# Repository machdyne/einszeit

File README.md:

# Einszeit

Einszeit is an open-source security device intended to provide information-theoretically secure (one-time-pad based) encryption between two or more paired devices over any communications medium.

> **Project status:** V1 hardware is in active development. See [Hardware Status](#hardware-status) and [Software Status](#software-status) below before using this project for anything beyond bench testing.

## Hardware Status

**V1: design complete, hardware tested.** Built around the RP2350 microcontroller. Boards have been fabricated, bench validated and entropy-tested. The design files are in `pcb/einszeit_v1` (schematic: `pcb/einszeit_v1.pdf`).

### Architecture

V1 is built around the **RP2350** microcontroller, chosen primarily for its documented, dedicated TRNG peripheral.

- **Entropy source:** RP2350's built-in TRNG block (Arm IP), which samples an internal free-running ring oscillator and claims compliance with FIPS 140-2, BSI AIS-31, and NIST SP 800-90B. Nominal entropy rate is ~7.5 kb/s at 150 MHz core clock.
- **Key storage:** key material never leaves the device, except on a microSD card, which is also how keys are exchanged.

### Why a raw TRNG

One-time-pad key material needs close to full entropy in every output bit. The random number generator of a typical secure element is not a raw entropy tap: it is the output of an internal DRBG (deterministic random bit generator), seeded periodically from a physical noise source. Its output entropy is bounded by the infrequently refreshed seed, not by the number of bytes read out, so it is architecturally unsuited to one-time-pad keys. Einszeit therefore uses the RP2350's TRNG, whose raw output can be tested directly.

One limitation remains: the TRNG is closed Arm IP, so its internal construction cannot be independently validated.

A secondary, physically independent entropy source (e.g. a discrete noise circuit) is not currently planned, but remains a possible future defense-in-depth addition if the RP2350 TRNG's characteristics warrant it.

Full entropy source documentation, extraction method, and validation results have been published alongside V1 firmware.

## Software Status

V1 software is complete enough for bench use with two devices, and is being tested on V1 hardware. It is not yet audited: do not use it for real secrets.

- **The device's terminal interface.** Connect any terminal program (PuTTY, screen, minicom, Tera Term) to the device's USB serial port:
  - Home shows the device at a glance;
  - Keys is a key manager: new keys, import and export on a transfer card, spare copies, delete;
  - Send and Receive encrypt and decrypt messages of up to 64 KiB, typed or pasted, or transferred as files by ZMODEM or XMODEM (detected automatically).

  See the [user interface document](docs/einszeit-ui.md) (EZ-UI-001).
- **`ez`, the host CLI** (`sw/ez`), over USB HID: scripting, and messages above 64 KiB. Build with `cmake -S sw -B build/sw && cmake --build build/sw`.
- **Firmware images** (`fw/einszeit`):
  - `einszeit_composite`: the terminal interface plus `ez`;
  - `einszeit_cdc`: the terminal interface only;
  - `einszeit_hid`: `ez` only.

  None of them has a software path into the bootloader; this is checked at build time. `einszeit_dev` adds development commands and hardware tests, and must never be used for real secrets.
- **Where keys are kept:**
  - on the **card** (microSD), in two copies, which the device checks and repairs by itself (the card mirror);
  - in the device's **internal storage**, alone or as a **spare copy** of a card key.

  Every 4 KiB of key is checked against its integrity tag before use, so a damaged or wrong card can cost a key but never secrecy. Keys leave the device only on a card.
- **A portable core** (`core/`), shared by the firmware and the host tests: offsets committed to F-RAM before any key byte is used, quarantine, an event log, key generation with online entropy monitoring, and buffered and streaming encryption.
- **Testing:**
  - on the host (`tests/run.sh`) against simulated hardware, with power loss, bit flips and card removal at every step;
  - an SD card emulator running the firmware's own driver;
  - screen tests of the terminal interface;
  - interoperability tests of the file transfers against lrzsz;
  - fuzzing.

  See [tests/README.md](tests/README.md).

Still open: the entropy assessment (OI-04), Windows support (OI-05), and an audit. See the [open items](docs/einszeit-implementation-spec.md#13-open-items).

Specifications and records: [security requirements](docs/einszeit-security-requirements.md) (EZ-SEC-001), [implementation specification](docs/einszeit-implementation-spec.md) (EZ-IMPL-001), [user interface](docs/einszeit-ui.md) (EZ-UI-001), [entropy thresholds](docs/einszeit-entropy-thresholds.md), [deviations](docs/einszeit-deviations.md) (EZ-DEV-001), [traceability](docs/einszeit-traceability.md) (EZ-TRACE-001).

## Security Model

Einszeit's core claim is that, given genuine full-entropy key material and correct one-time use, message confidentiality is information-theoretically secure — i.e., secure regardless of an adversary's computational power. This claim depends entirely on:

1. The entropy source(s) actually delivering full min-entropy per output bit (not merely passing statistical randomness tests, which a well-built DRBG would also pass).
2. Conditioning/extraction functions that don't reintroduce a computational-hardness dependency where an information-theoretic one is claimed (e.g., preferring universal-hash/Leftover-Hash-Lemma-based extraction over hash-based conditioning where the strict claim matters).
3. Correct one-time use of key material and secure erasure after use.

## AI Disclosure

This project makes use of LLMs for documentation, specifications, firmware and software. Once the project is stable, a human audit will be performed resulting in a code freeze that must not be directly modified by any LLM without an additional human audit. See our [GenAI session summaries](docs/genai).

## Funding

This project was partially funded through the NGI0 Commons Fund, a fund established by NLnet with financial support from the European Commission's Next Generation Internet programme.

## License

The contents of this repo are released under the [CERN-OHL-P](LICENSE.txt) license with the following exceptions:

 * The hidapi library (`sw/hidapi.c`, `sw/hidapi.h`) is BSD licensed.
 * The FatFs library (`third_party/fatfs`) is released under the FatFs license by ChaN, a 1-clause BSD-style license; see [third_party/fatfs/LICENSE.txt](third_party/fatfs/LICENSE.txt).
 * The Zetta editor (`third_party/zetta`) is released under the BSD-1-Clause license; see [third_party/zetta/LICENSE.md](third_party/zetta/LICENSE.md).

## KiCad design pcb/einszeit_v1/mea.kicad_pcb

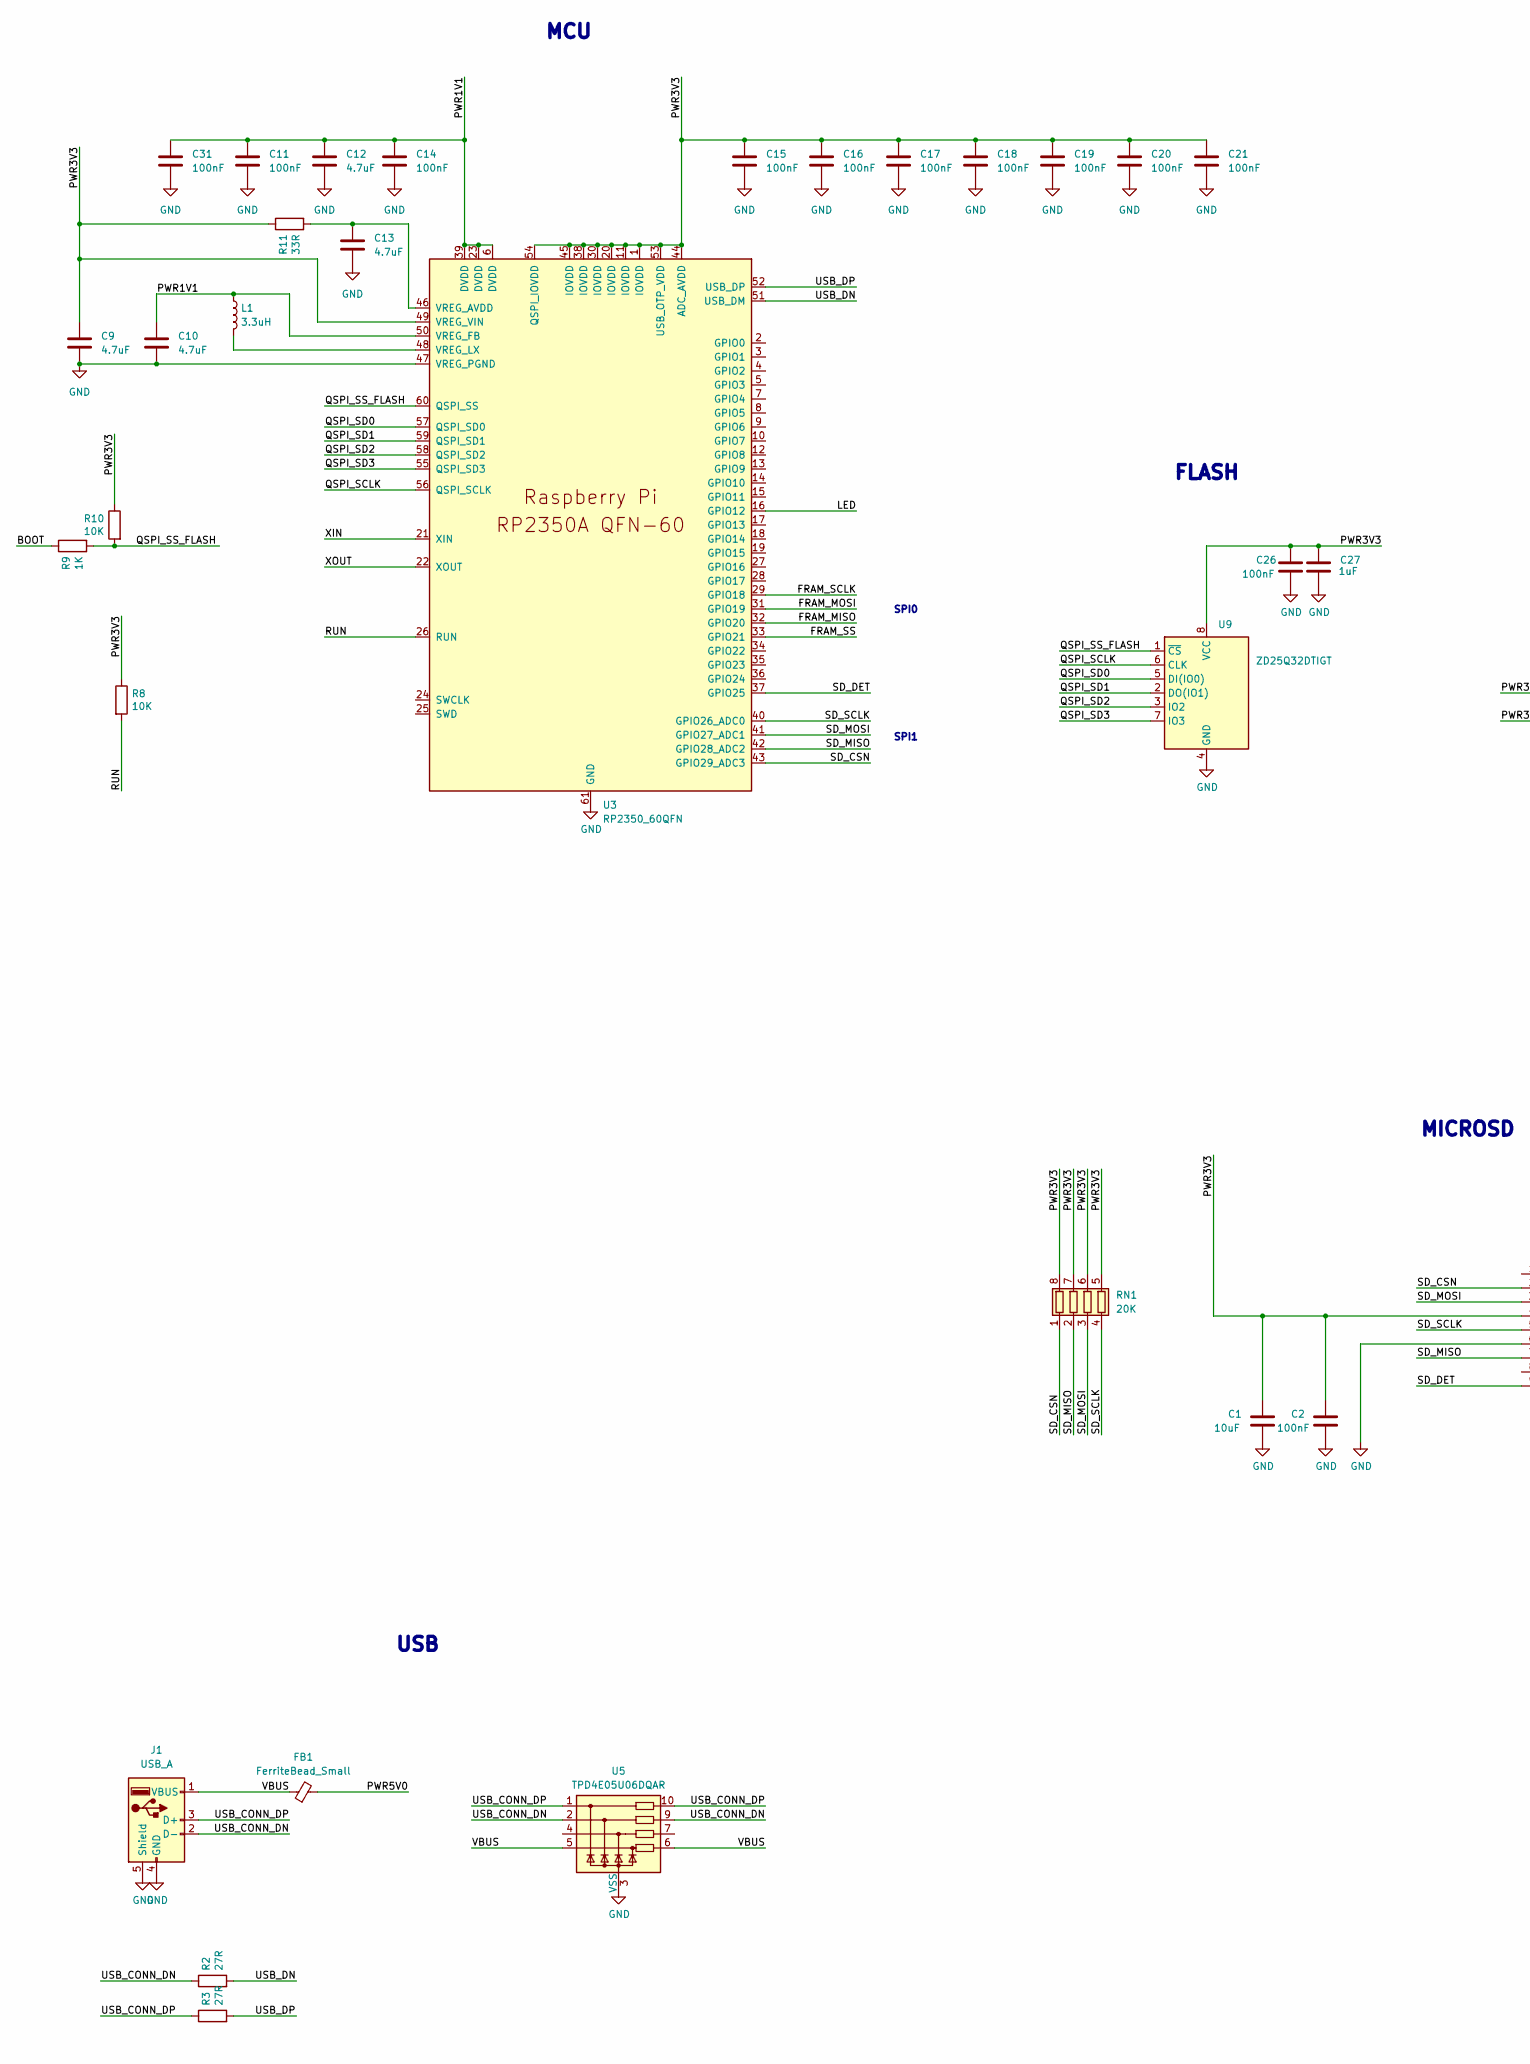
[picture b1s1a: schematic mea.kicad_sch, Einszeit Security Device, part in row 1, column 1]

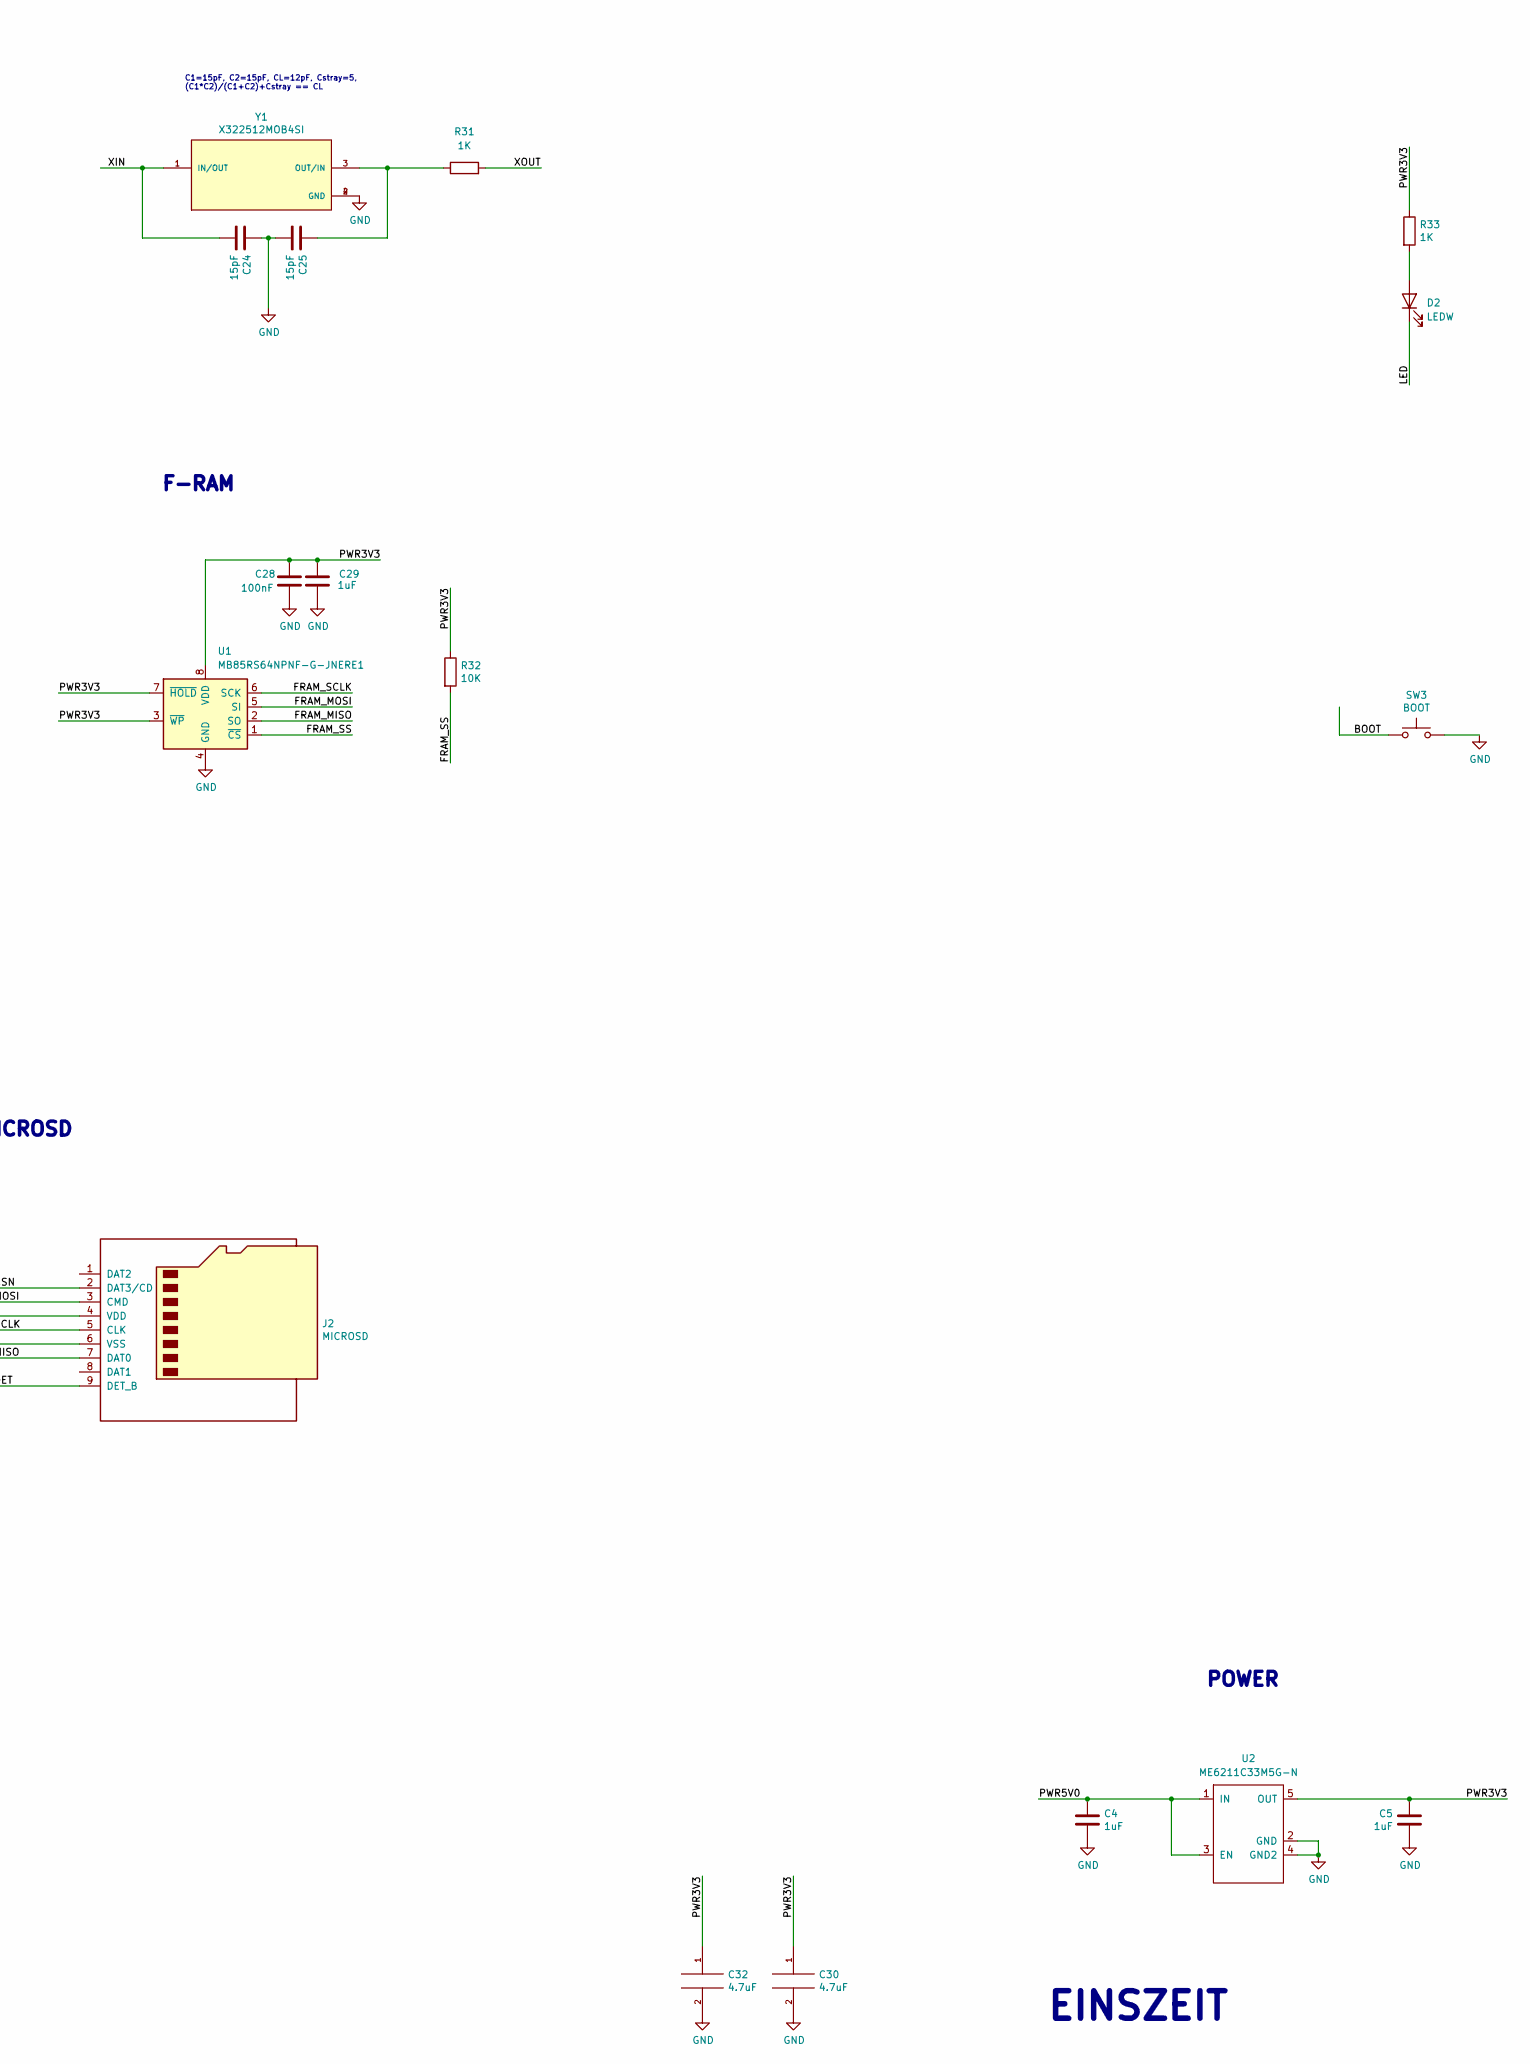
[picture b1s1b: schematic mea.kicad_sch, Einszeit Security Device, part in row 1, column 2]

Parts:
C1: 10uF; C_0402_1005Metric
C2, C11, C14, C15, C16, C17, C18, C19, C20, C21, C26, C28, C31: 100nF; C_0402_1005Metric
C4, C5, C27, C29: 1uF; C_0402_1005Metric
C9, C10, C12, C13, C30, C32: 4.7uF; C_0402_1005Metric
C24, C25: 15pF; C_0402_1005Metric
D2: LEDW; LED_0603_1608Metric
FB1: FerriteBead_Small; R_0402_1005Metric
J1: USB_A; USB_A_CNCTech_1001-011-01101_Horizontal
J2: MICROSD; TF-018B-H15-HAND-SOLDER
L1: 3.3uH; L_Murata_DFE201610P
R2, R3: 27R; R_0402_1005Metric
R8, R10, R32: 10K; R_0402_1005Metric
R9, R31, R33: 1K; R_0402_1005Metric
R11: 33R; R_0402_1005Metric
RN1: 20K; R_Array_Convex_4x0402
SW3: BOOT; Button_2P_3x4mm
U1: MB85RS64NPNF-G-JNERE1; SOIC-8_3.9x4.9mm_P1.27mm
U2: ME6211C33M5G-N; TSOP-5_1.65x3.05mm_P0.95mm
U3: RP2350_60QFN; RP2350-QFN-60-1EP_7x7_P0.4mm_EP3.4x3.4mm_ThermalVias
U5: TPD4E05U06DQAR; Diodes_UDFN-10_1.0x2.5mm_P0.5mm
U9: ZD25Q32DTIGT; SOIC-8_3.9x4.9mm_P1.27mm
Y1: X322512MOB4SI; XTAL_ECS-240-8-33-AGN-TR

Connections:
/BOOT: R9.1, SW3.1
/FRAM_MISO: U1.2 (SO), U3.32 (GPIO20)
/FRAM_MOSI: U1.5 (SI), U3.31 (GPIO19)
/FRAM_SCLK: U1.6 (SCK), U3.29 (GPIO18)
/FRAM_SS: R32.2, U1.1 (~CS), U3.33 (GPIO21)
/LED: D2.1 (K), U3.16 (GPIO12)
/PWR1V1: C10.1, C11.1, C12.1, C14.1, C31.1, L1.1, U3.6 (DVDD), U3.23 (DVDD), U3.39 (DVDD), U3.50 (VREG_FB)
/PWR3V3: C1.1, C2.1, C5.1, C9.1, C15.1, C16.1, C17.1, C18.1, C19.1, C20.1, C21.1, C26.1, C27.1, C28.1, C29.1, C30.1, C32.1, J2.4 (VDD), R8.1, R10.1, R11.1, R32.1, R33.1, RN1.5 (R4.2), RN1.6 (R3.2), RN1.7 (R2.2), RN1.8 (R1.2), U1.3 (~WP), U1.7 (~HOLD), U1.8 (VDD), U2.5 (OUT), U3.1 (IOVDD), U3.11 (IOVDD), U3.20 (IOVDD), U3.30 (IOVDD), U3.38 (IOVDD), U3.44 (ADC_AVDD), U3.45 (IOVDD), U3.49 (VREG_VIN), U3.53 (USB_OTP_VDD), U3.54 (QSPI_IOVDD), U9.8 (VCC)
/PWR5V0: C4.1, FB1.2, U2.1 (IN), U2.3 (EN)
/QSPI_SCLK: U3.56 (QSPI_SCLK), U9.6 (CLK)
/QSPI_SD0: U3.57 (QSPI_SD0), U9.5 (DI(IO0))
/QSPI_SD1: U3.59 (QSPI_SD1), U9.2 (DO(IO1))
/QSPI_SD2: U3.58 (QSPI_SD2), U9.3 (IO2)
/QSPI_SD3: U3.55 (QSPI_SD3), U9.7 (IO3)
/QSPI_SS_FLASH: R9.2, R10.2, U3.60 (QSPI_SS), U9.1 (~CS)
/RUN: R8.2, U3.26 (RUN)
/SD_CSN: J2.2 (DAT3/CD), RN1.1 (R1.1), U3.43 (GPIO29_ADC3)
/SD_DET: J2.9 (DET_B), U3.37 (GPIO25)
/SD_MISO: J2.7 (DAT0), RN1.2 (R2.1), U3.42 (GPIO28_ADC2)
/SD_MOSI: J2.3 (CMD), RN1.3 (R3.1), U3.41 (GPIO27_ADC1)
/SD_SCLK: J2.5 (CLK), RN1.4 (R4.1), U3.40 (GPIO26_ADC0)
/USB_CONN_DN: J1.2 (D-), R2.1, U5.2, U5.9
/USB_CONN_DP: J1.3 (D+), R3.1, U5.1, U5.10
/USB_DN: R2.2, U3.51 (USB_DM)
/USB_DP: R3.2, U3.52 (USB_DP)
/VBUS: FB1.1, J1.1 (VBUS), U5.5, U5.6
/XIN: C24.2, U3.21 (XIN), Y1.1 (IN/OUT)
/XOUT: R31.2, U3.22 (XOUT)
GND: C1.2, C2.2, C4.2, C5.2, C9.2, C10.2, C11.2, C12.2, C13.2, C14.2, C15.2, C16.2, C17.2, C18.2, C19.2, C20.2, C21.2, C24.1, C25.2, C26.2, C27.2, C28.2, C29.2, C30.2, C31.2, C32.2, J1.4 (GND), J1.5 (Shield), J2.6 (VSS), SW3.2, U1.4 (GND), U2.2 (GND), U2.4 (GND2), U3.47 (VREG_PGND), U3.61 (GND), U5.3 (VSS), U5.8 (VSS), U9.4 (GND), Y1.2 (GND), Y1.4 (GND)
unnamed: D2.2 (A), R33.2
unnamed: C13.1, R11.2, U3.46 (VREG_AVDD)
unnamed: L1.2, U3.48 (VREG_LX)
unnamed: C25.1, R31.1, Y1.3 (OUT/IN)

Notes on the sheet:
F-RAM
POWER
MICROSD
C1=15pF, C2=15pF, CL=12pF, Cstray=5, (C1*C2)/(C1+C2)+Cstray == CL
MCU
SPI0
FLASH
EINSZEIT
SPI1
USB

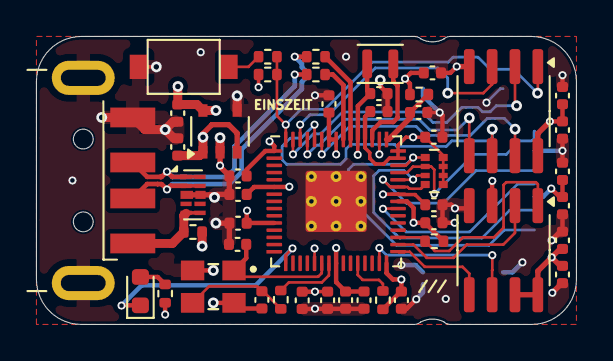
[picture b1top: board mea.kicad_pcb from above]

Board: 4 copper layers, 30.0 x 16.0 mm, 48 parts (1 on the bottom side), 33 nets.

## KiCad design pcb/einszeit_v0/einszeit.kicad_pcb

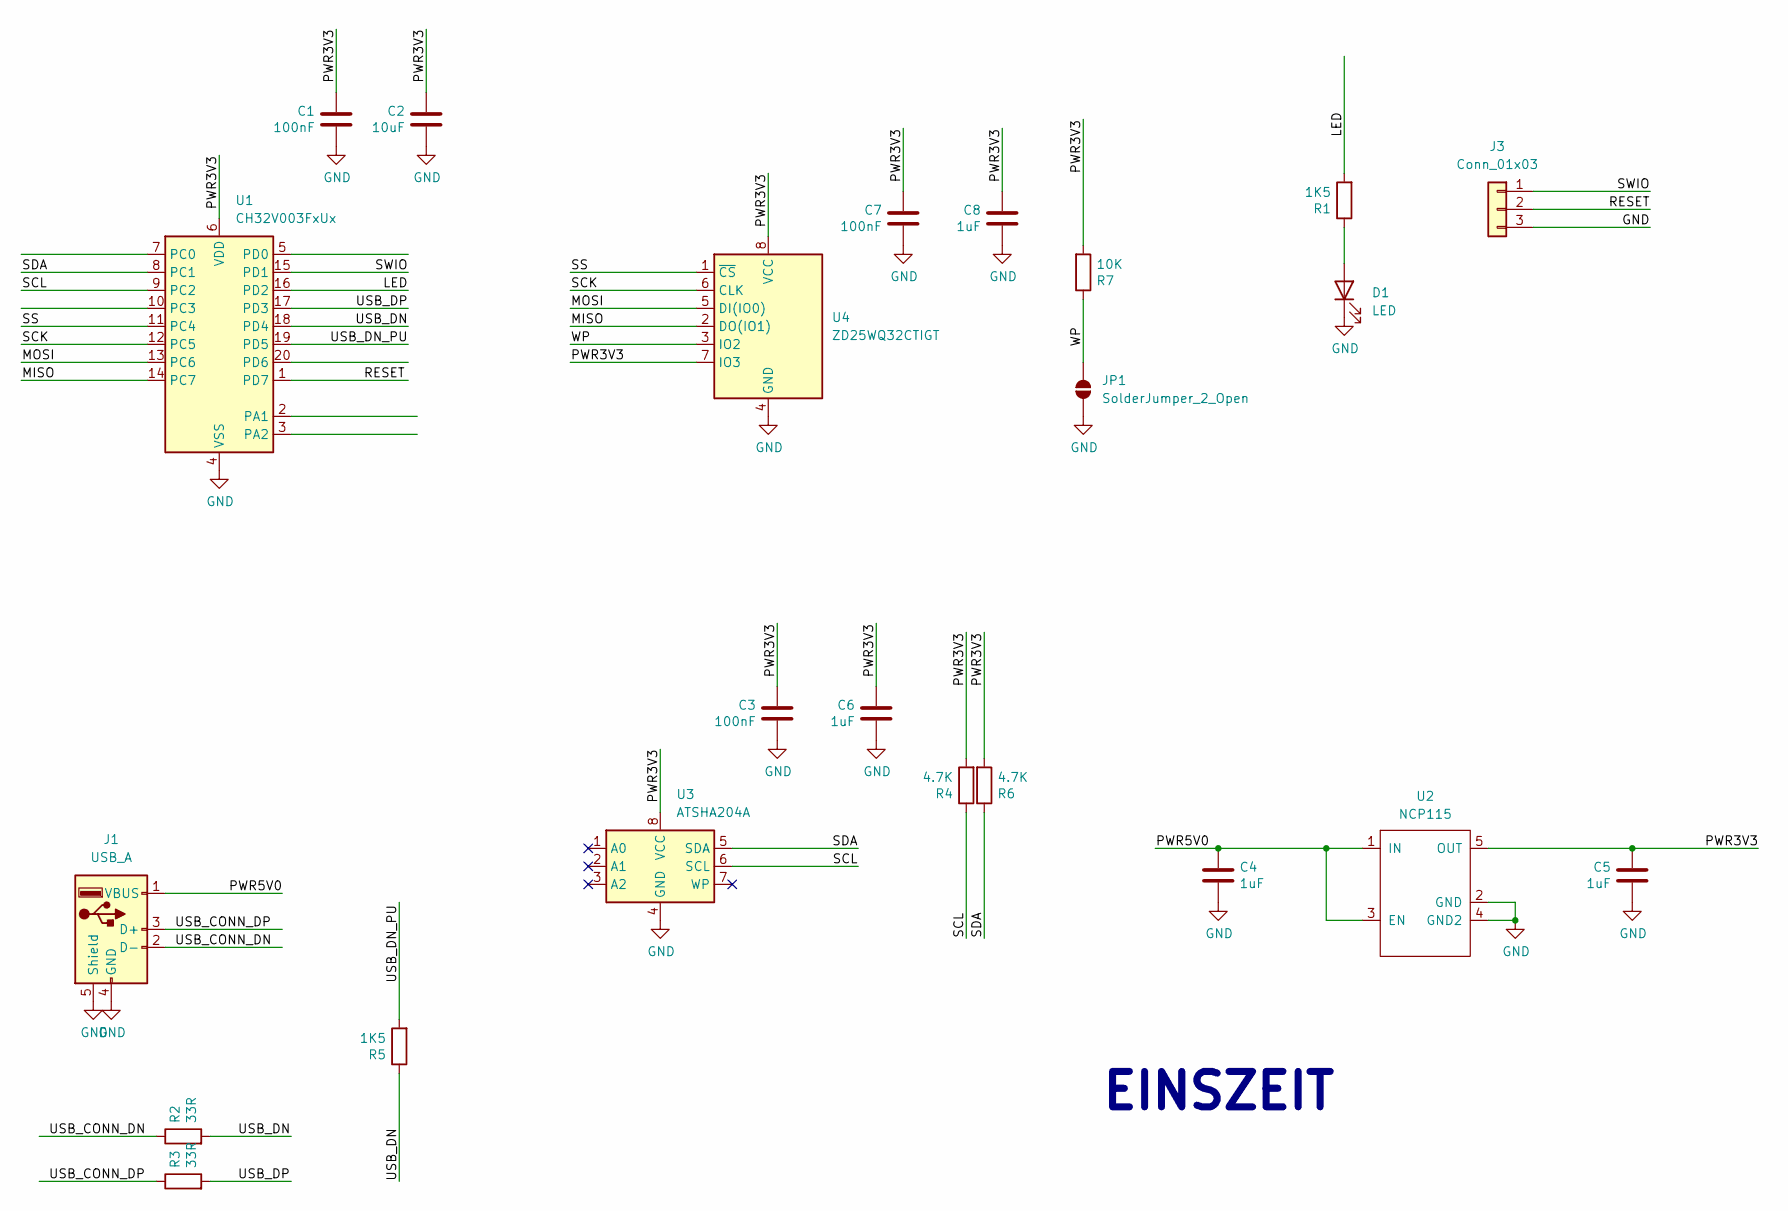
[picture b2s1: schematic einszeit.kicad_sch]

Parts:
C1, C3, C7: 100nF; C_0402_1005Metric
C2: 10uF; C_0402_1005Metric
C4, C5, C6, C8: 1uF; C_0402_1005Metric
D1: LED; LED_0603_1608Metric
J1: USB_A; USB_A_CNCTech_1001-011-01101_Horizontal
J3: Conn_01x03; PinHeader_1x03_P2.54mm_Vertical
JP1: SolderJumper_2_Open; SolderJumper-2_P1.3mm_Open_Pad1.0x1.5mm
R1, R5: 1K5; R_0402_1005Metric
R2, R3: 33R; R_0402_1005Metric
R4, R6: 4.7K; R_0402_1005Metric
R7: 10K; R_0402_1005Metric
U1: CH32V003FxUx; QFN-20-1EP_3x3mm_P0.4mm_EP1.65x1.65mm
U2: NCP115; TSOP-5_1.65x3.05mm_P0.95mm
U3: ATSHA204A; SOIC-8_3.9x4.9mm_P1.27mm
U4: ZD25WQ32CTIGT; SOP-8_3.9x4.9mm_P1.27mm

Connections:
/LED: R1.2, U1.16 (PD2)
/MISO: U1.14 (PC7), U4.2 (DO(IO1))
/MOSI: U1.13 (PC6), U4.5 (DI(IO0))
/PWR3V3: C1.1, C2.1, C3.1, C5.1, C6.1, C7.1, C8.1, R4.2, R6.2, R7.2, U1.6 (VDD), U2.5 (OUT), U3.8 (VCC), U4.7 (IO3), U4.8 (VCC)
/PWR5V0: C4.1, J1.1 (VBUS), U2.1 (IN), U2.3 (EN)
/RESET: J3.2, U1.1 (PD7)
/SCK: U1.12 (PC5), U4.6 (CLK)
/SCL: R4.1, U1.9 (PC2), U3.6 (SCL)
/SDA: R6.1, U1.8 (PC1), U3.5 (SDA)
/SS: U1.11 (PC4), U4.1 (~CS)
/SWIO: J3.1, U1.15 (PD1)
/USB_CONN_DN: J1.2 (D-), R2.1
/USB_CONN_DP: J1.3 (D+), R3.1
/USB_DN: R2.2, R5.1, U1.18 (PD4)
/USB_DN_PU: R5.2, U1.19 (PD5)
/USB_DP: R3.2, U1.17 (PD3)
/WP: JP1.2 (B), R7.1, U4.3 (IO2)
GND: C1.2, C2.2, C3.2, C4.2, C5.2, C6.2, C7.2, C8.2, D1.1 (K), J1.4 (GND), J1.5 (Shield), J3.3, JP1.1 (A), U1.4 (VSS), U1.21 (VSS), U2.2 (GND), U2.4 (GND2), U3.4 (GND), U4.4 (GND)
unnamed: D1.2 (A), R1.1

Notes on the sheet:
EINSZEIT

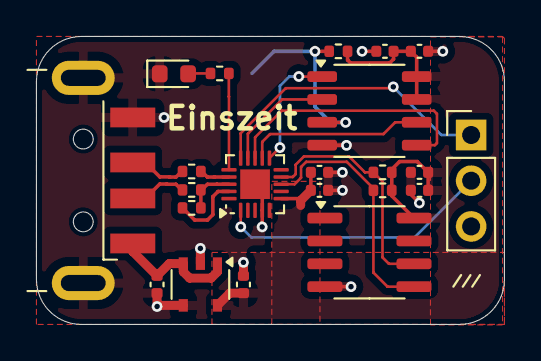
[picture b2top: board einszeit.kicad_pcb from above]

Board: 2 copper layers, 26.0 x 16.0 mm, 23 parts (1 on the bottom side), 19 nets.

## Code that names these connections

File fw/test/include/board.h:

/*
 * board.h -- Einszeit V1 (RP2350A) board definition
 *
 * Pin assignment supplied by the hardware author. Both SPI buses land on
 * their native hardware SPI functions, so no PIO is required:
 *
 *   GPIO18 = SPI0 SCK   GPIO19 = SPI0 TX   GPIO20 = SPI0 RX   GPIO21 = SPI0 CSn
 *   GPIO26 = SPI1 SCK   GPIO27 = SPI1 TX   GPIO28 = SPI1 RX   GPIO29 = SPI1 CSn
 *
 * Chip selects are driven as plain GPIO so that multi-byte transactions can
 * hold CS low across several spi_write_blocking() calls.
 */

/*
 * EZ-SEC-001 traceability (see docs/EZ-TEST-TRACEABILITY.md):
 *   SEC-HW-003  firmware storage and key data storage share no medium:
 *               firmware is in QSPI flash, key data is on the microSD.
 *   SEC-HW-002  SD_DET is the removal-detection input required by this
 *               requirement; its polarity is unconfirmed (gap G-02).
 *
 * Bench validation firmware. Not a production artifact.
 */
#ifndef EZ_BOARD_H
#define EZ_BOARD_H

#include "hardware/spi.h"

/* ---- FRAM (SPI0) ------------------------------------------------------- */
#define FRAM_SPI        spi0
#define FRAM_SCLK_PIN   18
#define FRAM_MOSI_PIN   19
#define FRAM_MISO_PIN   20
#define FRAM_SS_PIN     21      /* external 10K pull-up */

/* Conservative default; `fram bench` finds the real ceiling. */
#define FRAM_BAUD_DEFAULT   (8 * 1000 * 1000)
#define FRAM_BAUD_INIT      (1 * 1000 * 1000)

/* ---- microSD (SPI1) ---------------------------------------------------- */
#define SD_SPI          spi1
#define SD_DET_PIN      25
#define SD_SCLK_PIN     26      /* external 20K pull-up */
#define SD_MOSI_PIN     27      /* external 20K pull-up */
#define SD_MISO_PIN     28      /* external 20K pull-up */
#define SD_CSN_PIN      29      /* external 20K pull-up */

#define SD_BAUD_INIT    (400 * 1000)    /* card spec: 100-400 kHz during init */
#define SD_BAUD_DEFAULT (12 * 1000 * 1000)

/*
 * Card-detect polarity is not documented in the V1 schematic notes we were
 * given. `sd det` reports the raw level and watches for transitions so the
 * polarity can be determined empirically on the bench; set this once known.
 * 1 = pin reads low when a card is present (switch to GND, the common case).
 */
#ifndef SD_DET_ACTIVE_LOW
#define SD_DET_ACTIVE_LOW 1
#endif

/* ---- Status LED -------------------------------------------------------- */
#define LED_PIN         12

/* ---- Capture buffer ---------------------------------------------------- */
/*
 * RP2350A has 520 KB of SRAM. 192 KB = 1,572,864 bits, comfortably above the
 * 1,000,000-sample floor NIST SP 800-90B asks for on a binary source, and
 * also enough for a full 1000x1000 restart matrix (125 KB).
 */
#define EZ_CAP_MAX      (192u * 1024u)

#endif /* EZ_BOARD_H */

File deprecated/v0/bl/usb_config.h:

#ifndef _USB_CONFIG_H
#define _USB_CONFIG_H

//Defines the number of endpoints for this device. (Always add one for EP0). For two EPs, this should be 3.  For one, 2.
#define ENDPOINTS 2

/*	
	CH32V003FUN DevBoard:
	PD3 D+
	PD4 D-
	PD5 D-_PU

	CH32V003J4M6:
	PC1 D+
	PC2 D-
	PC4 D-_PU
*/

#define USB_PORT D     // [A,C,D] GPIO Port to use with D+, D- and DPU
#define USB_PIN_DP 3   // [0-4] GPIO Number for USB D+ Pin
#define USB_PIN_DM 4   // [0-4] GPIO Number for USB D- Pin
//#define USB_PORT_DPU A  // [A,C,D] Override GPIO Port for DPU
#define USB_PIN_DPU 5  // [0-7] GPIO for feeding the 1.5k Pull-Up on USB D- Pin; Comment out if not used / tied to 3V3!

#define RV003USB_OPTIMIZE_FLASH 1

#ifndef __ASSEMBLER__

#include <../fw/rv003usb/lib/tinyusb_hid.h>

#ifdef INSTANCE_DESCRIPTORS
//Taken from http://www.usbmadesimple.co.uk/ums_ms_desc_dev.htm
static const uint8_t device_descriptor[] = {
	18, //Length
	1,  //Type (Device)
	0x00, 0x02, //Spec (bcdUSB)
	0x0, //Device Class
	0x0, //Device Subclass
	0x0, //Device Protocol  (000 = use config descriptor)
	0x08, //Max packet size for EP0 (This has to be 8 because of the USB Low-Speed Standard)
	0x09, 0x12, //ID Vendor   //TODO: register this in http://pid.codes/howto/ or somewhere.
	0x03, 0xb0, //ID Product
	0x00, 0x00, //ID Rev (bcdDevice)
	1, //Manufacturer string
	2, //Product string
	3, //Serial string
	1, //Max number of configurations
};


static const uint8_t special_hid_desc[] = { 
  HID_USAGE_PAGE ( HID_USAGE_PAGE_DESKTOP      )                 ,
  HID_USAGE      ( 0xff  )                 , // Needed?
  HID_COLLECTION ( HID_COLLECTION_APPLICATION )                 ,
    HID_REPORT_SIZE ( 8 ),
    HID_REPORT_COUNT ( 127 ) ,
    HID_REPORT_ID    ( 0xaa                                   )
    HID_USAGE        ( 0xff              ) ,
    HID_FEATURE      ( HID_DATA | HID_ARRAY | HID_ABSOLUTE    ) ,
  HID_COLLECTION_END
};


static const uint8_t config_descriptor[] = {  //Mostly stolen from a USB mouse I found.
	// configuration descriptor, USB spec 9.6.3, page 264-266, Table 9-10
	9, 					// bLength;
	2,					// bDescriptorType;
	0x22, 0x00,			// wTotalLength  	

	//34, 0x00, //for just the one descriptor
	
	0x01,					// bNumInterfaces (Normally 1)  (If we need an additional HID interface add here)
	0x01,					// bConfigurationValue
	0x00,					// iConfiguration
	0x80,					// bmAttributes (was 0xa0)
	0x64,					// bMaxPower (200mA)


	//HID THING
	9,					// bLength
	4,					// bDescriptorType
	0,			// bInterfaceNumber (unused, would normally be used for HID)
	0,					// bAlternateSetting
	1,					// bNumEndpoints
	0x03,					// bInterfaceClass (0x03 = HID)
	0x00,					// bInterfaceSubClass
	0xff,					// bInterfaceProtocol
	0,					// iInterface

	9,					// bLength
	0x21,					// bDescriptorType (HID)
	0x10,0x01,		//bcd 1.1
	0x00, //country code
	0x01, //Num descriptors
	0x22, //DescriptorType[0] (HID)
	sizeof(special_hid_desc), 0x00, //Descriptor length XXX This looks wrong!!!

	7, //endpoint descriptor (For endpoint 1)
	0x05, //Endpoint Descriptor (Must be 5)
	0x81, //Endpoint Address
	0x03, //Attributes
	0x08,	0x00, //Size
	0xff, //Interval
};


//Ever wonder how you have more than 6 keys down at the same time on a USB keyboard?  It's easy. Enumerate two keyboards!

#define STR_MANUFACTURER u"cnlohr"
#define STR_PRODUCT      u"rv003usb"
#define STR_SERIAL       u"NBTT" // Need to change to BOOT when we finally decide on a flashing mechanism.

struct usb_string_descriptor_struct {
	uint8_t bLength;
	uint8_t bDescriptorType;
	const uint16_t wString[];
};

const static struct usb_string_descriptor_struct string0 __attribute__((section(".rodata"))) = {
	4,
	3,
	{0x0409}
};
const static struct usb_string_descriptor_struct string1 __attribute__((section(".rodata")))  = {
	sizeof(STR_MANUFACTURER),
	3,
	STR_MANUFACTURER
};
const static struct usb_string_descriptor_struct string2 __attribute__((section(".rodata")))  = {
	sizeof(STR_PRODUCT),
	3,
	STR_PRODUCT
};
const static struct usb_string_descriptor_struct string3 __attribute__((section(".rodata")))  = {
	sizeof(STR_SERIAL),
	3,
	STR_SERIAL
};


// This table defines which descriptor data is sent for each specific
// request from the host (in wValue and wIndex).
const static struct descriptor_list_struct {
	uint32_t	lIndexValue;
	const uint8_t	*addr;
	uint8_t		length;
} descriptor_list[] __attribute__((section(".rodata"))) = {
	{0x00000100, device_descriptor, sizeof(device_descriptor)},
	{0x00000200, config_descriptor, sizeof(config_descriptor)},
	{0x00002200, special_hid_desc, sizeof(special_hid_desc)},
	{0x00000300, (const uint8_t *)&string0, 4},
	{0x04090301, (const uint8_t *)&string1, sizeof(STR_MANUFACTURER)},
	{0x04090302, (const uint8_t *)&string2, sizeof(STR_PRODUCT)},	
	{0x04090303, (const uint8_t *)&string3, sizeof(STR_SERIAL)}
};
#define DESCRIPTOR_LIST_ENTRIES ((sizeof(descriptor_list))/(sizeof(struct descriptor_list_struct)) )

#endif // INSTANCE_DESCRIPTORS

#endif // __ASSEMBLER__
#endif 

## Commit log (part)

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2025-11-02 add render
2025-11-02 add schematic pdf
2026-05-19 change license to CERN-OHL-P

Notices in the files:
pcb/einszeit_v0/einszeit.kicad_sch:
Copyright © 2025 Lone Dynamics Corporation
pcb/einszeit_v1/mea.kicad_sch:
Copyright © 2026 Lone Dynamics Corporation
